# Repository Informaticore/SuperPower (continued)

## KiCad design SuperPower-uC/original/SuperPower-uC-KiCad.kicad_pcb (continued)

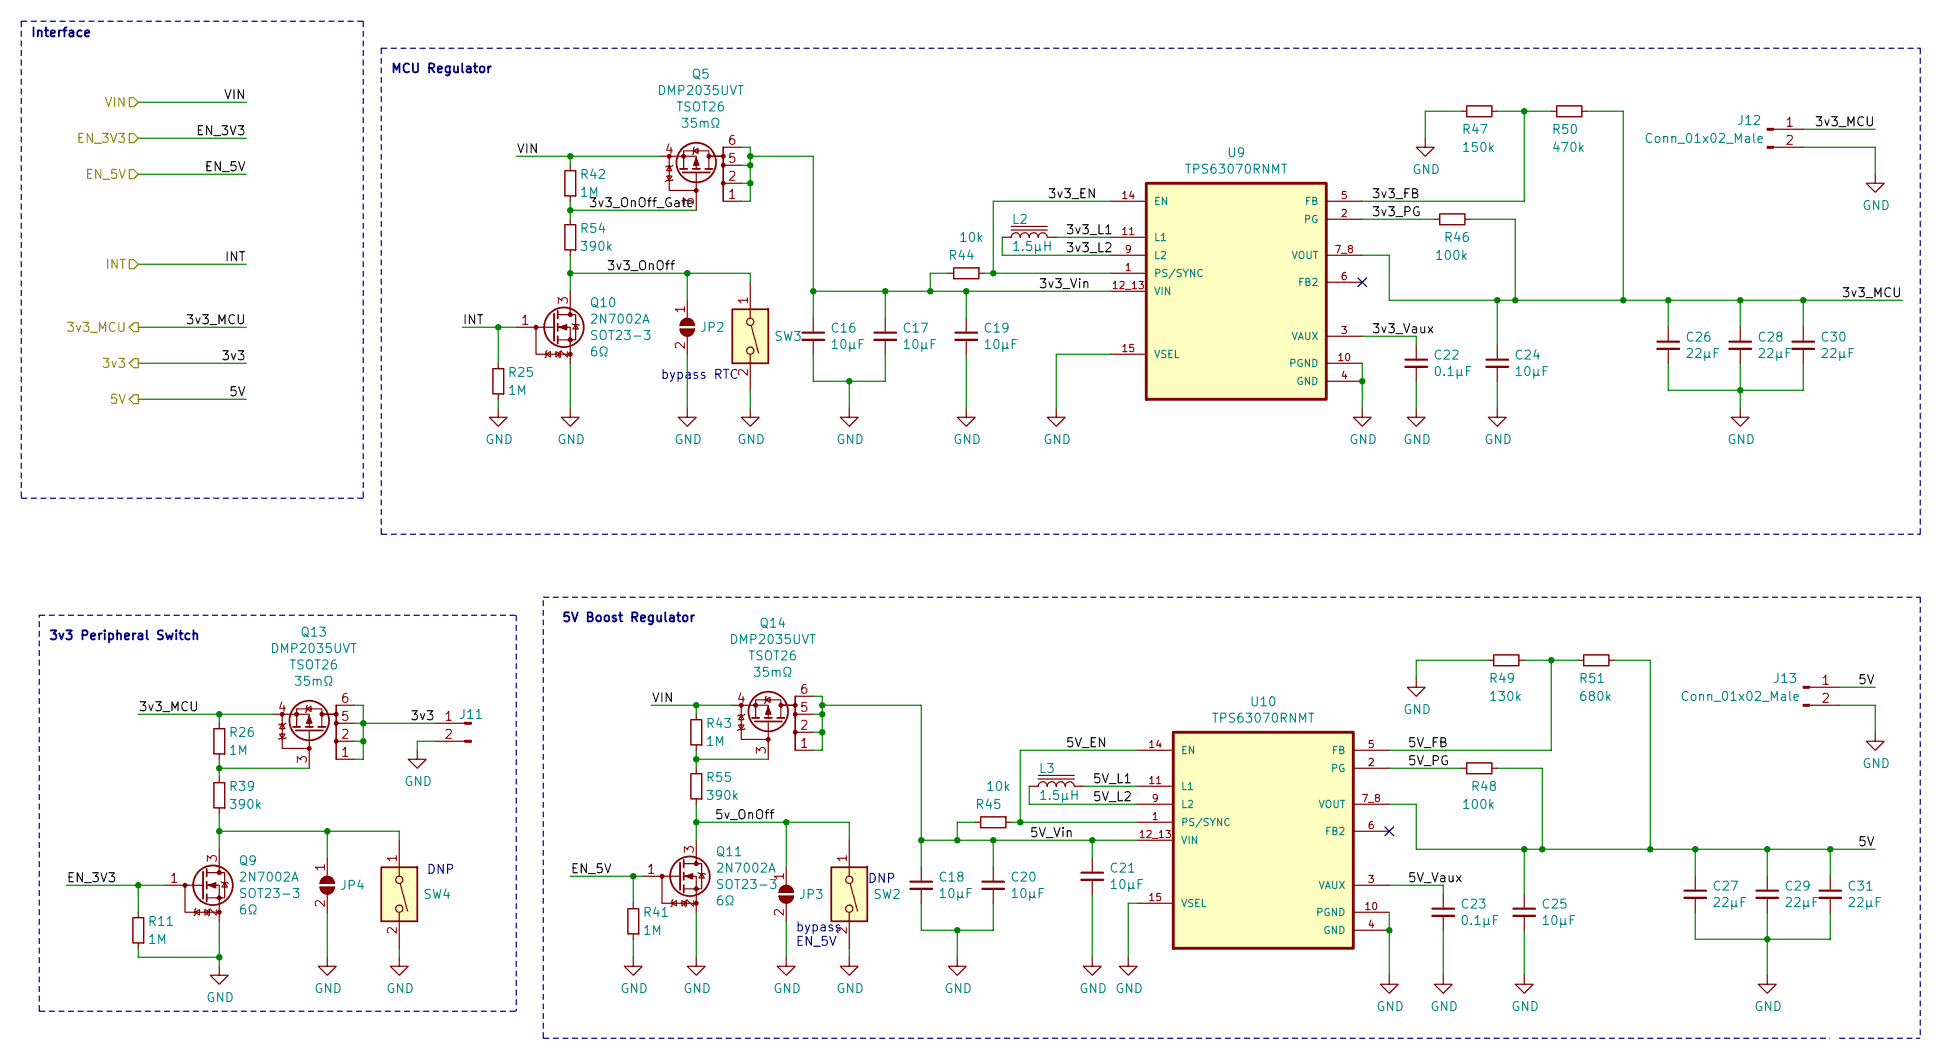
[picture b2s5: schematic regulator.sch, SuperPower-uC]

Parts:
C16, C17, C18, C19, C20, C21, C24, C25: 10μF; C_0805_2012Metric
C22, C23: 0.1µF; C_0603_1608Metric
C26, C27, C28, C29, C30, C31: 22μF; C_0805_2012Metric
J11, J12, J13: Conn_01x02_Male; PinSocket_1x02_P2.54mm_Vertical
JP2, JP3, JP4: SolderJumper_2_Open; SolderJumper-2_P1.3mm_Open_TrianglePad1.0x1.5mm
L2, L3: SPM6530T-1R5M; L_TDK_SPM6530T; Farnell_ref 2215610
Q5, Q13, Q14: DMP2035UVT; SOT-23-6; Farnell_ref 3405183
Q9, Q10, Q11: 2N7002A; SOT-23; Farnell_ref 3127180
R11, R25, R26, R41, R42, R43: 1M; R_0603_1608Metric
R39, R54, R55: 390k; R_0603_1608Metric
R44, R45: 10k; R_0603_1608Metric
R46, R48: 100k; R_0603_1608Metric
R47: 150k; R_0603_1608Metric
R49: 130k; R_0603_1608Metric
R50: 470k; R_0603_1608Metric
R51: 680k; R_0603_1608Metric
SW2, SW3, SW4: SW_DIP_x01; SW_DIP_SPSTx01_Slide_Copal_CHS-01A_W5.08mm_P1.27mm_JPin
U9, U10: TPS63070RNMT; VREG_TPS63070RNMR

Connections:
/MCU Module/3v3: J11.1, Q13.1 (D), Q13.2 (D), Q13.5 (D), Q13.6 (D); also elsewhere on the board
/MCU Module/3v3_MCU: C24.1, C26.1, C28.1, C30.1, J12.1, Q13.4 (S), R26.2, R46.2, R50.2, U9.7_8 (VOUT); also elsewhere on the board
/MCU Module/5V: C25.1, C27.1, C29.1, C31.1, J13.1, R48.2, R51.2, U10.7_8 (VOUT); also elsewhere on the board
/MCU Module/EN_3V3: Q9.1 (G), R11.2; also elsewhere on the board
/MCU Module/EN_5V: Q11.1 (G), R41.2; also elsewhere on the board
/RTC/INT: Q10.1 (G), R25.2; also elsewhere on the board
/Regulator and Cut-Off Module/3v3_EN: R44.1, U9.1 (PS/SYNC), U9.14 (EN)
/Regulator and Cut-Off Module/3v3_FB: R47.2, R50.1, U9.5 (FB)
/Regulator and Cut-Off Module/3v3_L1: L2.2, U9.11 (L1)
/Regulator and Cut-Off Module/3v3_L2: L2.1, U9.9 (L2)
/Regulator and Cut-Off Module/3v3_OnOff: JP2.1 (A), Q10.3 (D), R54.1, SW3.1
/Regulator and Cut-Off Module/3v3_OnOff_Gate: Q5.3 (G), R42.1, R54.2
/Regulator and Cut-Off Module/3v3_PG: R46.1, U9.2 (PG)
/Regulator and Cut-Off Module/3v3_Vaux: C22.1, U9.3 (VAUX)
/Regulator and Cut-Off Module/3v3_Vin: C16.1, C17.1, C19.1, Q5.1 (D), Q5.2 (D), Q5.5 (D), Q5.6 (D), R44.2, U9.12_13 (VIN)
/Regulator and Cut-Off Module/5V_EN: R45.1, U10.1 (PS/SYNC), U10.14 (EN)
/Regulator and Cut-Off Module/5V_FB: R49.2, R51.1, U10.5 (FB)
/Regulator and Cut-Off Module/5V_L1: L3.2, U10.11 (L1)
/Regulator and Cut-Off Module/5V_L2: L3.1, U10.9 (L2)
/Regulator and Cut-Off Module/5V_PG: R48.1, U10.2 (PG)
/Regulator and Cut-Off Module/5V_Vaux: C23.1, U10.3 (VAUX)
/Regulator and Cut-Off Module/5V_Vin: C18.1, C20.1, C21.1, Q14.1 (D), Q14.2 (D), Q14.5 (D), Q14.6 (D), R45.2, U10.12_13 (VIN)
/Regulator and Cut-Off Module/5v_OnOff: JP3.1 (A), Q11.3 (D), R55.1, SW2.1
/Regulator and Cut-Off Module/VIN: Q5.4 (S), Q14.4 (S), R42.2, R43.2; also elsewhere on the board
GND: C16.2, C17.2, C18.2, C19.2, C20.2, C21.2, C22.2, C23.2, C24.2, C25.2, C26.2, C27.2, C28.2, C29.2, C30.2, C31.2, J11.2, J12.2, J13.2, JP2.2 (B), JP3.2 (B), JP4.2 (B), Q9.2 (S), Q10.2 (S), Q11.2 (S), R11.1, R25.1, R41.1, R47.1, R49.1, SW2.2, SW3.2, SW4.2, U9.4 (GND), U9.10 (PGND), U9.15 (VSEL), U10.4 (GND), U10.10 (PGND), U10.15 (VSEL); also elsewhere on the board
unnamed: JP4.1 (A), Q9.3 (D), R39.1, SW4.1
unnamed: Q13.3 (G), R26.1, R39.2
unnamed: Q14.3 (G), R43.1, R55.2

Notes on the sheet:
Interface
5V Boost Regulator
bypass EN_5V
bypass RTC
MCU Regulator
3v3 Peripheral Switch
DNP

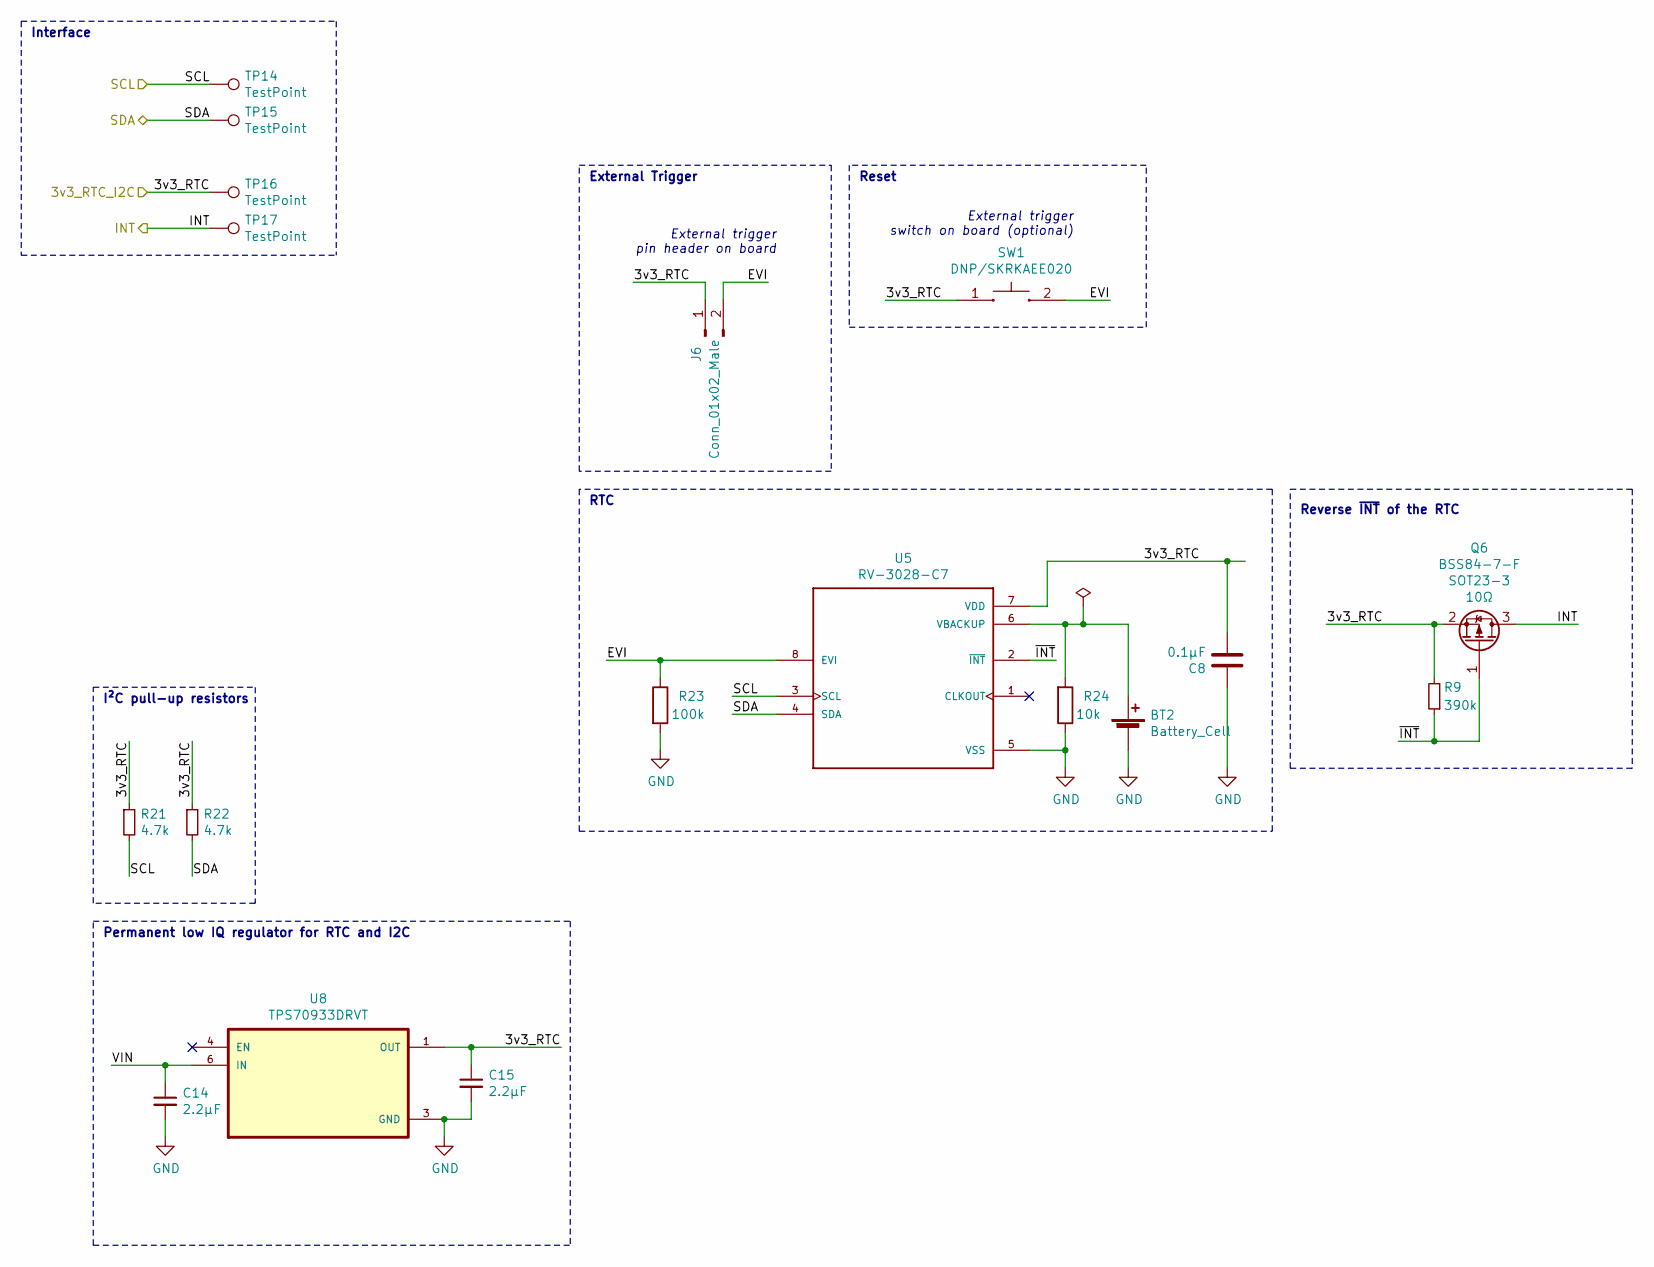
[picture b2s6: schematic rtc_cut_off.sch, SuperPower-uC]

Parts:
BT2: Battery_Cell; BatteryHolder_Keystone_3000_1x12mm
C8: 0.1µF; C_0603_1608Metric
C14, C15: 2.2μF; C_0603_1608Metric
J6: Conn_01x02_Male; PinHeader_1x02_P2.54mm_Vertical
Q6: BSS84-7-F; SOT-23; Farnell_ref 1843716
R9: 390k; R_0603_1608Metric
R21, R22: 4.7k; R_0603_1608Metric
R23: 100k; R_0603_1608Metric
R24: 10k; R_0603_1608Metric
SW1: DNP/SKRKAEE020; SKRKAEE020
TP14, TP15, TP16, TP17: TestPoint; TestPoint_Pad_D1.0mm
U5: RV-3028-C7; IC_RV-3028-C7
U8: TPS70933DRVT; SON65P200X200X80-7N

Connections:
/Charging Module/3v3_I2C: C8.2, C15.1, J6.1, Q6.2 (S), R9.2, R21.1, R22.1, SW1.1, TP16.1, U5.7 (VDD), U8.1 (OUT); also elsewhere on the board
/RTC/EVI: J6.2, R23.1, SW1.2, U5.8 (EVI)
/RTC/INT: Q6.3 (D), TP17.1; also elsewhere on the board
/RTC/VIN: C14.1, U8.6 (IN)
/RTC/~INT: Q6.1 (G), R9.1, U5.2 (~INT~)
/SCL: R21.2, TP14.1, U5.3 (SCL); also elsewhere on the board
/SDA: R22.2, TP15.1, U5.4 (SDA); also elsewhere on the board
GND: BT2.2 (-), C8.1, C14.2, C15.2, R23.2, R24.1, U5.5 (VSS), U8.3 (GND); also elsewhere on the board
unnamed: BT2.1 (+), R24.2, U5.6 (VBACKUP)

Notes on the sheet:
I²C pull-up resistors
External trigger pin header on board
Interface
External trigger switch on board (optional)
Permanent low IQ regulator for RTC and I2C
RTC
Reset
External Trigger
Reverse ~INT~ of the RTC

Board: 2 copper layers, 177 parts (7 on the bottom side), 114 nets, no tracks yet.

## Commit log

2020-10-06 annotated correctly
2020-11-01 designed a lowcostNoMcu version
    discarded mcu and ftdi ic
    simplified some stuff
    added standard 18650 battery connector
    ...
2020-11-03 fixed drc and erc errors
2020-12-22 Update Placement + Increase MTG Hole Size
2020-12-22 Shrink board height + Add Coin cell holder
2020-12-22 Convert 3D Board into Step + Draw a simple Box
2020-12-23 Make all connectors on only 2 sides.
    + Move DC Jack Connector to avoid having pads in conflict with the battery holder body.
2020-12-23 Update USB-C 3D footprint link
2020-12-23 Update DC Power Jack connector
    Add 3D Model
2020-12-23 Add JST ZH 3D Model
2020-12-23 Update 3D Board + Case
2020-12-23 Update DMP3028LSD SO-8 3D Package
2020-12-23 Update DMN3018SSD SO-8 3D Package
2020-12-24 Update 18650 Battery Holder 3D Model
    + Board 3D Model + 3D box
2020-12-24 Add a second optional Schottky diode for High Current
2020-12-26 Update components Placement
    RTC + 3.3 LDO + single raw connectors (x2)
2020-12-26 Update SKRKAEE020 tactile switch 3D footprint
2020-12-26 Update RV-3028-C7 3D Footprint
2020-12-26 Update TPS709xx series 3D footprint
2020-12-26 Update Single rows Headers to be fully compatible with ESP WROOM modules
    (ESP-32 DevKit C rev. 4)
2020-12-26 Update Placement + Add some labels
    +3.3V Buck-Boost DC-DC converter
2020-12-27 Update Placement USB_UART_Bridge
    + Misc.
2020-12-27 Update LTC4162-L components placement
    + Misc.
2020-12-27 Update components Placement
    +5V Buck-Boost + Misc.
2020-12-29 Add some DIP switch 1 way (x3)
    + add optionnal on board 0603 NTC + misc.
2020-12-30 Update 3D Board + Box
2020-12-30 Misc.
